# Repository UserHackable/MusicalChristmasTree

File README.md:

## Musical Charlieplex Christmas Tree

The idea behind this board is that it would allow you to create a wearable that would be both decorative and blinky, as well as be able to play a tune.. 
## MusicalChristmasTree 

### Board dimensions

* (300000, 200000) original units
* (3.0000, 2.0000) inches
* (76.2000, 50.8000) mm

[gerbers](%*_gerber.zip)

| Front | Back |
| --- | --- |
|  |  |

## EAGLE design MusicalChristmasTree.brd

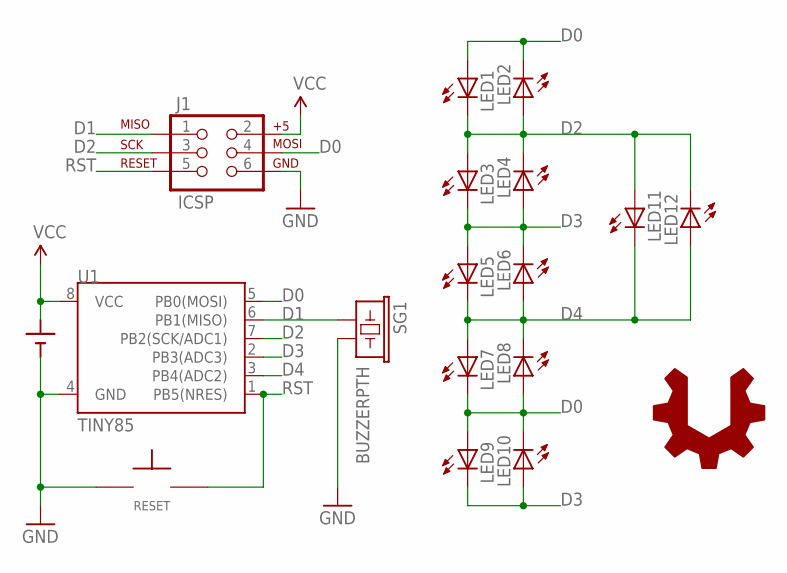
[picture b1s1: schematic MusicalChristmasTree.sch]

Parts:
BATT: CR2032; CR2032-THRU
J1: ICSP; 2X3-NS
LED1, LED2, LED3, LED4, LED5, LED6, LED7, LED8, LED9, LED10, LED11, LED12: LED5MM
RESET: TAC_SPST_NO
SG1: BUZZERPTH; BUZZER-12MM
U1: TINY85; DIP08
U$1: USER_HACKABLE

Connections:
D0: J1.4 (MOSI), LED1.A, LED2.K (C), LED7.K (C), LED8.A, LED9.A, LED10.K (C), U1.5 (PB0(MOSI))
D1: J1.1 (MISO), SG1.+ (1), U1.6 (PB1(MISO))
D2: J1.3 (SCK), LED1.K (C), LED2.A, LED3.A, LED4.K (C), LED11.A, LED12.K (C), U1.7 (PB2(SCK/ADC1))
D3: LED3.K (C), LED4.A, LED5.A, LED6.K (C), LED9.K (C), LED10.A, U1.2 (PB3(ADC3))
D4: LED5.K (C), LED6.A, LED7.A, LED8.K (C), LED11.K (C), LED12.A, U1.3 (PB4(ADC2))
GND: BATT.-, J1.6 (GND), RESET.P$1, SG1.- (2), U1.4 (GND)
RST: J1.5 (RST), RESET.P$2, U1.1 (PB5(NRES))
VCC: BATT.+1 (+), J1.2 (V+), U1.8 (VCC)

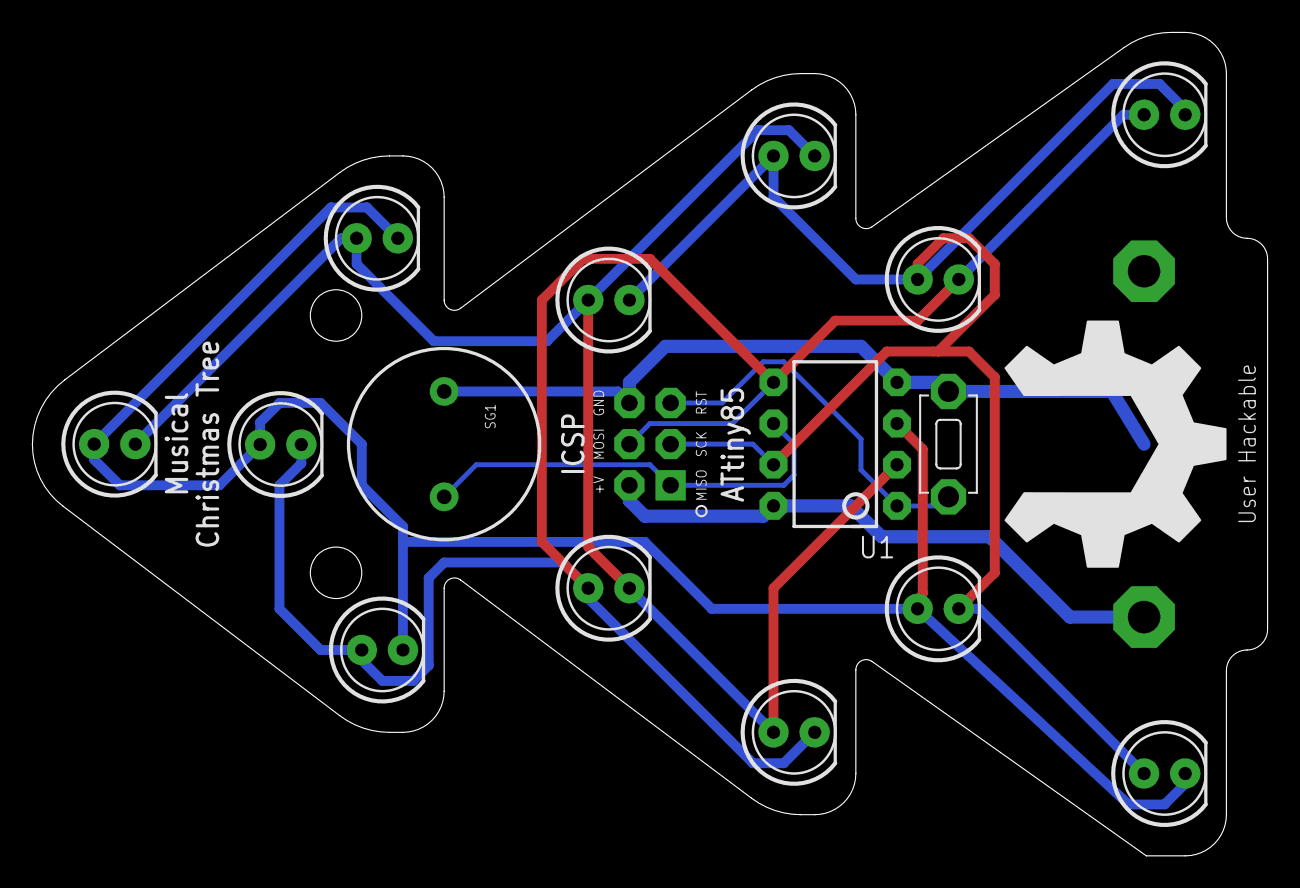
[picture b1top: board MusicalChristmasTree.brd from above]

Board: 2 copper layers, 76.2 x 50.8 mm, 18 parts (1 on the bottom side), 8 nets.

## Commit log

2016-04-08 from Makefile
2016-04-08 removing temp files
2016-04-08 removing swp

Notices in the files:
parts and their libraries:
SparkFun-DigitalIC: Licensing: Creative Commons ShareAlike 4.0 International - https://creativecommons.org/licenses/by-sa/4.0
